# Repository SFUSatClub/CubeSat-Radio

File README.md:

# CubeSat-Radio
KiCad project of the cubesat radio test article in preparation for the Canadian Satellite Design Challenge

This repository uses the SFU Satellite Team's KiCad component library as a submodule.
To start working on the repository:

```
1. Open the git shell
2. Navigate to the directory you wish to place the repository inside
3. git clone --recursive "https://github.com/SFUSatClub/CubeSat-Radio.git"
4. cd .\CubeSat-Radio\KiCad-Lib\
5. git checkout master
```

If you modify either the component schematic or footprint libraries you must push those changes to the SFUSatClub/KiCad-Lib repository.

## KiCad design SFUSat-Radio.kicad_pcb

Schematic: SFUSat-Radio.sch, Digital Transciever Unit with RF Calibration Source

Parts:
C41, C42: 100nF; C_0402; Ratings AEC-Q200; Tolerance ±20%; Manufacturer Part Numbe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 CGA2B1X7R1C104M050BC
C413, C422, C513, C522: 39pF; C_0402; Tolerance ±5%; Voltage - Rated 50V; Manufacturer Part Numbe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 GRM1555C1H390JA01D
C414: 22pF; C_0402; Part Number GRM1555C1H220JZ01E; Digi-Key 490-11382-1-ND
C415, C416, C429, C430, C431, C432, C433, C434, C519, C529, C530, C531, C532, C533, C534: DNF; C_0402
C417, C420: 10pF; C_0402; Part Number GJM1555C1H100JB01D; Digi-Key 490-3113-1-ND
C418: 2.2uF; C_0402; Part Number JMK105BJ225MVHF; Digi-Key 587-3710-1-ND
C419, C518: 27pF; C_0402; Tolerance ±5%; Voltage - Rated 50V; Manufacturer Part Numbe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 GRM1555C1H270JA01D
C421: 1.2pF; C_0402; Part Number GJM1555C1H1R2BB01D; Digi-Key 490-8085-1-ND
C514: 7.5pF; C_0402; Tolerance ±0.1pF; Voltage - Rated 50V; Manufacturer Part Numbe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 GRM1555C1H7R5BA01D
C515: 15pF; C_0402; Tolerance ±5%; Voltage - Rated 50V; Manufacturer Part Numbe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 GJM1555C1H150JB01D
C516: 12pF; C_0402; Tolerance ±5%; Voltage - Rated 50V; Manufacturer Part Numbe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 GJM1555C1H120JB01D
C517: 10pF; C_0402; Tolerance ±5%; Voltage - Rated 50V; Manufacturer Part Numbe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 GJM1555C1H100JB01D
C520: 5.6pF; C_0402; Tolerance ±0.25pF; Voltage - Rated 50V; Manufacturer Part Numbe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 GJM1555C1H5R6CB01D
C521: 0.5pF; C_0402; Tolerance ±0.25pF; Voltage - Rated 50V; Manufacturer Part Numbe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 GJM1555C1HR50CB01D
D1, D3, D11: GREEN; LED_0603
J1: PC104-8BIT; PC104-8bit
J2, J3, J4, J5: PC104PTH
J6: SMA; SMA-Vert-TH
J7, J8, J9, J10, J11: TP_TH_150
J12, J13, J14, J400, J500: SMA; UFL-R-SMT-1-Coaxial-Connector; Digikey H9161-ND
J15, J25: Conn_01x02; Socket_Strip_Straight_1x02_Pitch2.54mm
L400: 8.2nH; L_0402; Part Number 0402CS-8N2XJLW; Digi-Key N/A
L401, L402, L403, L405: 0R0; L_0603; Part Number RMC1/16JPTP; Digi-Key N/A
L404: 12.55nH; L_1606; Part Number 1606-10J; Digi-Key N/A
L500: 2.7nH; L_0402; Manufacturer Part Numbe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 0402CS-2N7XJLW
L501, L502: 220R; L_0603; Current Rating (Max) 2A; Manufacturer Part Numbe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 BLM18EG221SN1D
L503: DNF; L_0603
L504: 5.6nH; L_1606; Manufacturer Part Numbe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 1606-6JLC
L505: 1.5nH; L_0603; Current Rating 500mA; Tolerance ±0.3nH; Manufacturer Part Numbe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 LQG18HN1N5S00D
P1: 3pin-DC-power; PJ-028-SMT-TR-3pin-DC-jack
R1, R2: 1k0-DNF; R_0402; Tolerance ±0.5%; Manufacturer Part Numbe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 ERA-2AED102X
R3, R13, R18: 287; R_0402
R600, R603, R605, R611, R612, R615: 0R; R_0402; Tolerance Jumper; Manufacturer Part Numbe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 AC0402JR-070RL
R601, R602, R604, R610, R613, R614: DNF; R_0402
U1, U400, U500: SINGLE_0402
U2: SKY13345-368LF; 12-UFQFN-PAD; Voltage - Supply 2.5 V ~ 5.5 V; Manufacturer Part Numbe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 SKY13345-368LF
U3: CD4555BPWR; TSSOP-16; Voltage - Supply 3 V ~ 18 V; Voltage Supply Source Dual Supply; Manufacturer Part Numbe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 CD4555BPWR
U101: 0433BM15A0001; U_0805-6; Mouser 609-0433BM15A0001E
U111: 0915BM15A0001E; U_0805-6; Mouser 609-0915BM15A0001E

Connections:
/3.3V Regulator/3V3OUT: J25.2; also elsewhere on the board
/3V1: J9.1, R18.1; also elsewhere on the board
/3V3: C41.1, C42.1, J1.3B, J1.29B, J8.1, J25.1, R1.1, R2.1, R3.1, R600.1, R602.1, R604.1, R610.1, R612.1, R614.1, U2.7, U3.16; also elsewhere on the board
/3V6: J7.1, L401.1, L402.1, L403.1, L501.1, L502.1, L503.1, R13.1; also elsewhere on the board
/5V0: J10.1; also elsewhere on the board
/CC1101_LB/RF_N: U101.3; also elsewhere on the board
/CC1101_LB/RF_P: U101.4; also elsewhere on the board
/CC1101_UB/RF_N: U111.3; also elsewhere on the board
/CC1101_UB/RF_P: U111.4; also elsewhere on the board
/EN_3V6: J1.12B, J15.1; also elsewhere on the board
/LB_HP_RX: U2.1; also elsewhere on the board
/LB_HP_TX: C422.1, U2.9
/LB_LP: J12.1 (INNER), U101.1; also elsewhere on the board
/LB_LP_TX: C413.2; also elsewhere on the board
/LB_RX0TX1: U3.2; also elsewhere on the board
/LB_TEST_TX: C419.1, C420.1, C421.1, C422.2, C432.1, C433.1, C434.1, L405.1
/MISO: J1.3A; also elsewhere on the board
/MOSI: J1.2A; also elsewhere on the board
/PA_LB/IN: C414.1; also elsewhere on the board
/PA_LB/OUT: C415.1, C416.1, C417.1, C429.1, C430.1, C431.1, L404.2, L405.2; also elsewhere on the board
/PA_UB/IN: C514.1; also elsewhere on the board
/PA_UB/OUT: C515.1, C516.1, C517.1, C529.1, C530.1, C531.1, L504.2, L505.1; also elsewhere on the board
/PKT_RCV: J1.5A; also elsewhere on the board
/SCL: J1.18B, R2.2; also elsewhere on the board
/SCLK: J1.1A; also elsewhere on the board
/SDA: J1.17B, R1.2; also elsewhere on the board
/Temp_sense_LB/A0: R600.2, R601.1; also elsewhere on the board
/Temp_sense_LB/A1: R602.2, R603.1; also elsewhere on the board
/Temp_sense_LB/A2: R604.2, R605.1; also elsewhere on the board
/Temp_sense_UB/A0: R610.2, R611.1; also elsewhere on the board
/Temp_sense_UB/A1: R612.2, R613.1; also elsewhere on the board
/Temp_sense_UB/A2: R614.2, R615.1; also elsewhere on the board
/UB_HP_TX: C522.1, U2.3
/UB_LP: C513.2, J13.1 (INNER), U111.1
/UB_RX0TX1: U3.3; also elsewhere on the board
/UB_TEST_TX: C519.1, C520.1, C521.1, C522.2, C532.1, C533.1, C534.1, L505.2
/V1: U2.4, U3.4
/V2: U2.5, U3.5
/V3: U2.6, U3.6
/VIN: J1.28A, J1.29A, J15.2, P1.1; also elsewhere on the board
/~LB_CS: J1.4A; also elsewhere on the board
/~UB_CS: J1.6A; also elsewhere on the board
GND: C41.2, C42.2, C415.2, C416.2, C417.2, C418.1, C419.2, C420.2, C421.2, C429.2, C430.2, C431.2, C432.2, C433.2, C434.2, C515.2, C516.2, C517.2, C518.1, C519.2, C520.2, C521.2, C529.2, C530.2, C531.2, C532.2, C533.2, C534.2, D1.1, D3.1, D11.1, J1.1B, J1.2B, J1.31B, J1.32A, J1.32B, J2.1, J3.1, J4.1, J5.1, J6.2 (OUTER), J11.1, J12.2 (OUTER), J13.2 (OUTER), J14.2 (OUTER), J400.2 (OUTER), J500.2 (OUTER), L400.2, L500.2, P1.2, P1.3, R601.2, R603.2, R605.2, R611.2, R613.2, R615.2, U2.2, U2.8, U2.10, U2.12, U2.13, U3.1, U3.8, U3.15, U101.2, U101.5, U101.6, U111.2, U111.5, U111.6; also elsewhere on the board
unnamed: C413.1, C414.2, L400.1
unnamed: C418.2, L401.2, L402.2, L403.2, L404.1
unnamed: C513.1, C514.2, L500.1
unnamed: C518.2, L501.2, L502.2, L503.2, L504.1
unnamed: D1.2, R18.2
unnamed: D3.2, R3.2
unnamed: D11.2, R13.2
unnamed: J6.1 (INNER), U2.11
unnamed: J14.1 (INNER), U1.1
unnamed: J400.1 (INNER), U400.1
unnamed: J500.1 (INNER), U500.1

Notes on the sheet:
strange pkg
to antenna
LED List: 3V3 On 3V6 On 5V0 On 3V1 On UB Transmitting LB Transmitting Packet Ready
CTRL
TX/RX Truth Table
Path
REF 10*
REF 11*
REF 4**
REF 5**
435Mhz Lower Band (LB)
790MHz Upper Band (UB)
REF 60*
REF 61*
ADDR: 0x4A
ADDR: 0x49
UB_RX0TX1
LB_RX0TX1
Antenna feed select truth table

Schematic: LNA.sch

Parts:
C3, C11: 100pF; C_0402; Part Number GRM1555C1H101JA01D; Digi-Key 490-5922-1-ND
C4, C9: 390pF; C_0402; Part Number GRM1555C1H391JA01J; Digi-Key 490-6236-1-ND
C5, C6: 0.01uF; C_0402; Part Number GRM155R71E103KA01D; Digi-Key 490-1312-1-ND
C7, C8: 56pF; C_0402; Part Number GRM1555C1H560JA01D; Digi-Key 490-1288-1-ND
C10: 0.1uF; C_0402; Part Number GRM155R71C104KA88D; Digi-Key 490-3261-1-ND
J16: SMA; UFL-R-SMT-1-Coaxial-Connector; Digikey H9161-ND
L1: 22nH; L_0402; Part Number 0402CS-22NXGLW; Digi-Key N/A
L2: 4.3nH; L_0402; Part Number 0402CS-4N3XGLW; Digi-Key N/A
L3: 24nH; L_0402; Part Number 0402CS-24NXGLW; Digi-Key N/A
R5: 0R05; C_0603; Part Number BLM18EG221SN1D; Digi-Key 490-3992-1-ND
R6: 1210; R_0402; Part Number RC0402FR-071K21L; Digi-Key 311-1.21KLRCT-ND
R7: 100; R_0402; Part Number RC0402FR-07100RL; Digi-Key 311-100LRCT-ND
U5: MML09211H; 8-VFDFN; Part Number MML09211HT1; Digi-Key MML09211HT1CT-ND
U6: SINGLE_0402

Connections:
/5V0: R5.1; also elsewhere on the board
/LB_HP_RX: C11.1; also elsewhere on the board
/LB_LP_RX: C3.2; also elsewhere on the board
GND: C4.2, C5.2, C6.2, C7.2, C9.2, C10.2, J16.2 (OUTER), U5.9; also elsewhere on the board
unnamed: C3.1, L1.1, L2.2
unnamed: C4.1, C6.1, L1.2, U5.3
unnamed: C8.1, R7.2
unnamed: C8.2, U5.5
unnamed: C5.1, C7.1, C9.1, C10.1, L3.1, R5.2, R6.1
unnamed: C11.2, L3.2, R7.1, U5.6, U5.7
unnamed: J16.1 (INNER), U6.1
unnamed: L2.1, U5.1
unnamed: R6.2, U5.4

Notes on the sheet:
Ferrite bead, 220 Ohm @ 100MHz

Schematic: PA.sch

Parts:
C401, C412: 10uF; C_TANT_1411; Tolerance ±10%; Voltage - Rated 16V; Manufacturer Part Numbe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 TAJB106K016RNJ
C402, C407, C408, C409: 1uF; C_0402; Part Number GRM155R61A105KE15D; Digi-Key 490-12701-1-ND
C403: 10uF; C_TANT_2312; Tolerance ±20%; Voltage - Rated 25V; Manufacturer Part Numbe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 TAJC106M025RNJ
C404, C410: 2.2uF; C_0402; Part Number JMK105BJ225MVHF; Digi-Key 587-3710-1-ND
C405: 0.33uF; C_0402; Tolerance ±10%; Voltage - Rated 10V; Manufacturer Part Numbe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 CL05A334KP5NNNC
C406: 220pF; C_0402; Part Number GRM1555C1H221JA01E; Digi-Key 490-1293-1-ND
C411: DNF; C_0402; Part Number GRM155R61A105KE15D; Digi-Key 490-12701-1-ND
C428, C523, C524, C525, C526, C527: DNF; C_0402
J401, J402, J404, J405, J406: TP_TH_150
R401, R409: 220R; R_0402; Part Number RMC1/16S-221JTH; Digi-Key N/A
R402, R403: 390R; R_0402; Part Number RMC1/16S-391JTH; Digi-Key N/A
R404: 1K; R_0402; Part Number RC0402JR-071KL; Digi-Key 311-1.0KJRCT-ND
R405, R406, R407, R408: 10K; R_0402; Part Number RC0402JR-0710KL; Digi-Key 311-10KJRCT-ND
R410: 100k; R_0805; Tolerance ±1%; Manufacturer Part Numbe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 ERJ-6ENF1003V
R411: DNF; R_0805
RV401: CT6EP103; Tolerance ±10%; Manufacturer Part Numbe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 CT6EP103
SH500: BMI-S-205-F; Manufacturer Part Numbe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 BMI-S-205-F
U401: LMV358; TSSOP-8_4.4x3mm_Pitch0.65mm; Part Number LMV358IYDT; Digi-Key 497-10524-1-ND
U402: RF6886; QFN-24; Part Number RF6886TR13; Digi-Key 689-1091-1-ND

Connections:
/3V1: R410.1, RV401.1, U401.8; also elsewhere on the board
/3V6: C403.1, C406.1, C409.1, C428.1, C523.1, C524.1, C525.1, C526.1, C527.1, R402.2, R403.2, U402.1, U402.2, U402.3, U402.22; also elsewhere on the board
/PA_LB/GAIN: J406.1, R410.2, R411.1, RV401.2, U401.3
/PA_LB/IN: U402.6; also elsewhere on the board
/PA_LB/OUT: U402.13, U402.14, U402.15, U402.16, U402.17, U402.18; also elsewhere on the board
/PA_LB/PWR_REF: C408.1, J405.1, R403.1, R408.1, U402.24
/PA_LB/PWR_SENSE: C407.1, J404.1, R402.1, R407.1, U402.23
/PA_LB/VREG: C401.1, C402.1, C405.2, C411.1, C412.1, J401.1, R401.2, R409.1, U401.1
GND: C401.2, C402.2, C403.2, C404.2, C406.2, C407.2, C408.2, C409.2, C410.2, C411.2, C412.2, C428.2, C523.2, C524.2, C525.2, C526.2, C527.2, R406.2, R411.2, RV401.3, SH500.1, SH500.2, SH500.3, SH500.4, SH500.5, SH500.6, SH500.7, SH500.8, SH500.9, SH500.10, SH500.11, SH500.12, SH500.13, SH500.14, SH500.15, SH500.16, SH500.17, SH500.18, SH500.19, SH500.20, U401.4, U402.7, U402.8, U402.9, U402.10, U402.11, U402.12, U402.CP; also elsewhere on the board
unnamed: C404.1, R401.1, U402.5
unnamed: C405.1, R404.2, U401.2
unnamed: C410.1, R409.2, U402.19
unnamed: J402.1, R404.1, R405.2, U401.7
unnamed: R405.1, R407.2, U401.6
unnamed: R406.1, R408.2, U401.5

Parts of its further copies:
C501, C512: 10uF; C_TANT_1411; Tolerance ±10%; Voltage - Rated 16V; Manufacturer Part Numbe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 TAJB106K016RNJ
C502, C507, C508, C509: 1uF; C_0402; Part Number GRM155R61A105KE15D; Digi-Key 490-12701-1-ND
C503: 10uF; C_TANT_2312; Tolerance ±20%; Voltage - Rated 25V; Manufacturer Part Numbe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 TAJC106M025RNJ
C504, C510: 2.2uF; C_0402; Part Number JMK105BJ225MVHF; Digi-Key 587-3710-1-ND
C505: 0.33uF; C_0402; Tolerance ±10%; Voltage - Rated 10V; Manufacturer Part Numbe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 CL05A334KP5NNNC
C506: 220pF; C_0402; Part Number GRM1555C1H221JA01E; Digi-Key 490-1293-1-ND
J501, J502, J504, J505, J506: TP_TH_150
R501, R509: 220R; R_0402; Part Number RMC1/16S-221JTH; Digi-Key N/A
R502, R503: 390R; R_0402; Part Number RMC1/16S-391JTH; Digi-Key N/A
R504: 1K; R_0402; Part Number RC0402JR-071KL; Digi-Key 311-1.0KJRCT-ND
R505, R506, R507, R508: 10K; R_0402; Part Number RC0402JR-0710KL; Digi-Key 311-10KJRCT-ND
R510: 100k; R_0805; Tolerance ±1%; Manufacturer Part Numbe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 ERJ-6ENF1003V
RV501: CT6EP103; Tolerance ±10%; Manufacturer Part Numbe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 CT6EP103
SH400: BMI-S-205-F; Manufacturer Part Numbe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 BMI-S-205-F
U501: LMV358; TSSOP-8_4.4x3mm_Pitch0.65mm; Part Number LMV358IYDT; Digi-Key 497-10524-1-ND
U502: RF6886; QFN-24; Part Number RF6886TR13; Digi-Key 689-1091-1-ND

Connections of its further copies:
/3V1: R510.1, RV501.1, U501.8; also elsewhere on the board
/3V6: C503.1, C506.1, C509.1, R502.2, R503.2, U502.1, U502.2, U502.3, U502.22; also elsewhere on the board
/PA_UB/GAIN: J506.1, R510.2, RV501.2, U501.3; also elsewhere on the board
/PA_UB/IN: U502.6; also elsewhere on the board
/PA_UB/OUT: U502.13, U502.14, U502.15, U502.16, U502.17, U502.18; also elsewhere on the board
/PA_UB/PWR_REF: C508.1, J505.1, R503.1, R508.1, U502.24
/PA_UB/PWR_SENSE: C507.1, J504.1, R502.1, R507.1, U502.23
/PA_UB/VREG: C501.1, C502.1, C505.2, C512.1, J501.1, R501.2, R509.1, U501.1; also elsewhere on the board
GND: C501.2, C502.2, C503.2, C504.2, C506.2, C507.2, C508.2, C509.2, C510.2, C512.2, R506.2, RV501.3, SH400.1, SH400.2, SH400.3, SH400.4, SH400.5, SH400.6, SH400.7, SH400.8, SH400.9, SH400.10, SH400.11, SH400.12, SH400.13, SH400.14, SH400.15, SH400.16, SH400.17, SH400.18, SH400.19, SH400.20, U501.4, U502.7, U502.8, U502.9, U502.10, U502.11, U502.12, U502.CP; also elsewhere on the board
unnamed: C504.1, R501.1, U502.5
unnamed: C505.1, R504.2, U501.2
unnamed: C510.1, R509.2, U502.19
unnamed: J502.1, R504.1, R505.2, U501.7
unnamed: R505.1, R507.2, U501.6
unnamed: R506.1, R508.2, U501.5

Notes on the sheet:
Amplifier
Output Power Feedback
Output Power Control
R*05,R*06/R*07,R*08 * (Vref - Vsense) = Vout

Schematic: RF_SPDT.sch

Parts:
C12, C14, C15: 47pF; C_0402
C13: 47nF; C_0402
J17, J18: SMA; UFL-R-SMT-1-Coaxial-Connector; Digikey H9161-ND
U7: SKY13372-467LF; QFN-16_650P
U8, U11: SINGLE_0402
U17: 74LVC1G14SE-7; SOT353; Voltage - Supply 1.65 V ~ 5.5 V; Manufacturer Part Numbe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 74LVC1G14SE-7

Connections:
/3V3: C13.1, U7.1 (VDD), U17.5; also elsewhere on the board
/LB_LP: C12.1; also elsewhere on the board
/LB_LP_RX: C15.1; also elsewhere on the board
/LB_LP_TX: C14.1; also elsewhere on the board
/LB_RX0TX1: U17.2; also elsewhere on the board
GND: C13.2, J17.2 (OUTER), J18.2 (OUTER), U7.4 (GND), U7.5 (GND), U7.6 (GND), U7.7 (GND), U7.8 (GND), U7.10 (GND), U7.11 (GND), U7.13 (GND), U7.14 (GND), U7.15 (GND), U7.16 (GND), U7.17 (PAD), U17.3; also elsewhere on the board
unnamed: C12.2, U7.3 (RFC)
unnamed: C14.2, U7.12 (J1)
unnamed: C15.2, U7.9 (J2)
unnamed: J17.1 (INNER), U11.1
unnamed: J18.1 (INNER), U8.1
unnamed: U7.2 (VCTL), U17.4

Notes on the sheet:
CTRL
TX/RX Truth Table
Path
For U6, U8, and U10, place these pads on the PCB such that they are in between the pads of C19, C20 and C21 so a jumper can be placed at a 45 degree angle to test the RF path

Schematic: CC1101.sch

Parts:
C100, C103, C105, C106, C107: 100nF; C_0402
C101: 12pF; C_0402
C102: 15pF; C_0402
C104: 220pF; C_0402
R100: 56k; R_0402
U13: CONN_02X05_SHRD; Socket_Strip_Straight_2x05; Current Rating 3A; Manufacturer Part Numbe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 SBH11-PBPC-D05-ST-BK
U100: CC1101-Q1
X100: NX3225GA

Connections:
/3V3: C100.2, C103.2, C104.2, C105.2, C107.2, U13.2, U100.6, U100.9, U100.11, U100.15, U100.18, U100.21, U100.30, U100.31; also elsewhere on the board
/CC1101_LB/RF_N: U100.13; also elsewhere on the board
/CC1101_LB/RF_P: U100.12; also elsewhere on the board
/CC1101_UB/GDO0: U13.4; also elsewhere on the board
/CC1101_UB/OP_3.3: U13.9
/CC1101_UB/~RESET: U13.7
/LB_RX0TX1: U100.28; also elsewhere on the board
/MISO: U13.10, U100.26; also elsewhere on the board
/MOSI: U13.8, U100.23; also elsewhere on the board
/PKT_RCV: U100.3; also elsewhere on the board
/SCLK: U13.6, U100.25; also elsewhere on the board
/UB_RX0TX1: U13.3; also elsewhere on the board
/~LB_CS: U100.4; also elsewhere on the board
/~UB_CS: U13.5; also elsewhere on the board
GND: C100.1, C101.1, C102.1, C103.1, C104.1, C105.1, C106.2, C107.1, R100.2, U13.1, U100.1, U100.8, U100.10, U100.14, U100.19, U100.22, U100.29, U100.33; also elsewhere on the board
unnamed: C101.2, U100.5, X100.1
unnamed: C102.2, U100.7, X100.3
unnamed: C106.1, U100.2, U100.32
unnamed: R100.1, U100.20

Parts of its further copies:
C110, C113, C115, C116, C117: 100nF; C_0402
C111: 12pF; C_0402
C112: 15pF; C_0402
C114: 220pF; C_0402
R110: 56k; R_0402
U12: CONN_02X05_SHRD; Socket_Strip_Straight_2x05; Current Rating 3A; Manufacturer Part Numbe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 SBH11-PBPC-D05-ST-BK
U110: CC1101-Q1
X110: NX3225GA

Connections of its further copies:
/3V3: C110.2, C113.2, C114.2, C115.2, C117.2, U12.2, U110.6, U110.9, U110.11, U110.15, U110.18, U110.21, U110.30, U110.31; also elsewhere on the board
/CC1101_LB/OP_3.3: U12.9
/CC1101_LB/~RESET: U12.7
/CC1101_UB/GDO0: U110.3; also elsewhere on the board
/CC1101_UB/RF_N: U110.13; also elsewhere on the board
/CC1101_UB/RF_P: U110.12; also elsewhere on the board
/LB_RX0TX1: U12.3; also elsewhere on the board
/MISO: U12.10, U110.26; also elsewhere on the board
/MOSI: U12.8, U110.23; also elsewhere on the board
/PKT_RCV: U12.4; also elsewhere on the board
/SCLK: U12.6, U110.25; also elsewhere on the board
/UB_RX0TX1: U110.28; also elsewhere on the board
/~LB_CS: U12.5; also elsewhere on the board
/~UB_CS: U110.4; also elsewhere on the board
GND: C110.1, C111.1, C112.1, C113.1, C114.1, C115.1, C116.2, C117.1, R110.2, U12.1, U110.1, U110.8, U110.10, U110.14, U110.19, U110.22, U110.29, U110.33; also elsewhere on the board
unnamed: C111.2, U110.5, X110.1
unnamed: C112.2, U110.7, X110.3
unnamed: C116.1, U110.2, U110.32
unnamed: R110.1, U110.20

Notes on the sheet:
Place decoupling capacitors as close as possible to power pins
Required Power for Debugger operation
Optional 3V3 source
Unconnected
MISO, MOSI, and SCLK signal are the same for both upper and lower band CC1101. Care must be taken to prevent interference when multiple masters are connected.

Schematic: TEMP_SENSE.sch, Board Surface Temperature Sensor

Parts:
C600: DNF; C_0402
U600: STLM75; TSSOP-8-3x3mm-SOT505-1

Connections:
/3V3: C600.1, U600.8; also elsewhere on the board
/SCL: U600.2; also elsewhere on the board
/SDA: U600.1; also elsewhere on the board
/Temp_sense_LB/A0: U600.7; also elsewhere on the board
/Temp_sense_LB/A1: U600.6; also elsewhere on the board
/Temp_sense_LB/A2: U600.5; also elsewhere on the board
GND: C600.2, U600.4; also elsewhere on the board

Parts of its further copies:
U610: STLM75; TSSOP-8-3x3mm-SOT505-1

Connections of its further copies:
/3V3: U610.8; also elsewhere on the board
/SCL: U610.2; also elsewhere on the board
/SDA: U610.1; also elsewhere on the board
/Temp_sense_UB/A0: U610.7; also elsewhere on the board
/Temp_sense_UB/A1: U610.6; also elsewhere on the board
/Temp_sense_UB/A2: U610.5; also elsewhere on the board
GND: U610.4; also elsewhere on the board

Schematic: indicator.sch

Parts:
D420, D421: GREEN; LED_0603
J23, J24: TP_TH_150
R420, R421: 287; R_0402
U420: 2N7002DW; SOT-363

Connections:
/3V3: R420.1, R421.1; also elsewhere on the board
/5V0: J24.1; also elsewhere on the board
/LB_RX0TX1: U420.5 (G1); also elsewhere on the board
/PKT_RCV: U420.2 (G2); also elsewhere on the board
/UB_RX0TX1: J23.1; also elsewhere on the board
GND: U420.1 (S2), U420.4 (S1); also elsewhere on the board
unnamed: D420.1, U420.3 (D1)
unnamed: D420.2, R420.2
unnamed: D421.1, U420.6 (D2)
unnamed: D421.2, R421.2

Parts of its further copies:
D2, D4: GREEN; LED_0603
J21, J22: TP_TH_150
R8, R14: 287; R_0402
U14: 2N7002DW; SOT-363

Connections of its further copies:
/3V3: R8.1, R14.1; also elsewhere on the board
/5V0: U14.2 (G2); also elsewhere on the board
/LB_RX0TX1: J21.1; also elsewhere on the board
/PKT_RCV: J22.1; also elsewhere on the board
/UB_RX0TX1: U14.5 (G1); also elsewhere on the board
GND: U14.1 (S2), U14.4 (S1); also elsewhere on the board
unnamed: D2.1, U14.3 (D1)
unnamed: D2.2, R8.2
unnamed: D4.1, U14.6 (D2)
unnamed: D4.2, R14.2

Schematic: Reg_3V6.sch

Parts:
C1, C2, C16, C18, C19, C20: 10uF; C_1210; Tolerance ±10%; Voltage - Rated 16V; Manufacturer Part Numbe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 EMK325BJ106KN-T
C17, C21: 1nF; C_0402; Tolerance ±10%; Voltage - Rated 16V; Manufacturer Part Numbe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 GRM155R61C102KA01D
C22: 4.7uF; C_0805; Tolerance ±10%; Voltage - Rated 10V; Manufacturer Part Numbe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 GRM219R61A475KE34D
C23: 470nF; C_0402; Tolerance ±10%; Voltage - Rated 6.3V; Manufacturer Part Numbe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 GRM155R60J474KE19D
C24: 680pF; C_0402; Tolerance ±5%; Voltage - Rated 25V; Manufacturer Part Numbe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 GRM1555C1E681JA01D
C25: 100nF; C_0402; Tolerance ±10%; Voltage - Rated 6.3V; Manufacturer Part Numbe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 GRM155R60J104KA01D
C26, C27, C28, C29, C30: 47uF; C_1206; Tolerance ±10%; Voltage - Rated 6.3V; Manufacturer Part Numbe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 GRM31CR60J476KE19L
L4: 10uH; SLF6045; Current Rating 2.7A; Tolerance ±20%; Manufacturer Part Numbe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 SLF6045T-100M1R6-3PF
R4: 49k9; R_0805; Tolerance ±1%; Manufacturer Part Numbe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 ERJ-6ENF4992V
R9: 19K1; R_0805; Tolerance ±1%; Manufacturer Part Numbe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 ERJ-6ENF1912V
R10: 3.01R; R_0402; Tolerance ±1%; Manufacturer Part Numbe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 CRCW04023R01FKED
U4: LMS3635AQRNLRQ1; LMS3635AQRNLTQ1; Digikey 296-47482-1-ND

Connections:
/3.6V Regulator/BIAS: C25.1, R10.1, U4.22
/3.6V Regulator/BOOST: C23.1, U4.2
/3.6V Regulator/FB: C24.2, R4.2, R9.1, U4.21
/3.6V Regulator/SW: C23.2, L4.1, U4.9
/3V6: C24.1, C26.1, C27.1, C28.1, C29.1, C30.1, L4.2, R4.1, R10.2; also elsewhere on the board
/EN_3V6: U4.18; also elsewhere on the board
/VIN: C1.1, C2.1, C16.1, C17.1, C18.1, C19.1, C20.1, C21.1, U4.4, U4.14, U4.15; also elsewhere on the board
GND: C1.2, C2.2, C16.2, C17.2, C18.2, C19.2, C20.2, C21.2, C22.2, C25.2, C26.2, C27.2, C28.2, C29.2, C30.2, R9.2, U4.3, U4.5, U4.6, U4.7, U4.8, U4.10, U4.11, U4.12, U4.13, U4.16, U4.20; also elsewhere on the board
unnamed: C22.1, U4.1

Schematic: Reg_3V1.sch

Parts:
C31, C32: 1uF; C_0402; Part Number GRM155R61A105KE15D; Digi-Key 490-12701-1-ND
R11: 1K; R_0402; Part Number RC0402JR-071KL; Digi-Key 311-1.0KJRCT-ND
U9: TLV702; SOT_23_5; Part Number TLV70231DBVT; Digi-Key 296-27894-1-ND

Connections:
/3V1: C32.1, U9.5; also elsewhere on the board
/3V6: C31.1, R11.1, U9.1; also elsewhere on the board
GND: C31.2, C32.2, U9.2; also elsewhere on the board
unnamed: R11.2, U9.3

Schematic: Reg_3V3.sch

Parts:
C33: 100nF; C_0402
C34: DNF; C_0402
C35: 2.2uF; C_0402; Ratings AEC-Q200; Tolerance ±20%; Manufacturer Part Numbe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 JMK105BJ225MVHF
R12: 1k; R_0402
U10: TPS799; PDSO-G5

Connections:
/3.3V Regulator/3V3OUT: C35.1, U10.5 (OUT); also elsewhere on the board
/3V6: C33.1, R12.2, U10.1 (IN); also elsewhere on the board
GND: C33.2, C34.2, C35.2, U10.2 (GND); also elsewhere on the board
unnamed: C34.1, U10.4 (NR)
unnamed: R12.1, U10.3 (EN)

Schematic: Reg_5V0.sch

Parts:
C36: 2.2uF; C_0805; Tolerance ±10%; Voltage - Rated 10V; Manufacturer Part Numbe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 GRM21BR71A225KA01L
C37: 22uF; C_1206; Tolerance ±20%; Voltage - Rated 10V; Manufacturer Part Numbe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 GRM31CR61A226ME19L
C38: 100nF; C_0402; Ratings AEC-Q200; Tolerance ±20%; Manufacturer Part Numbe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 CGA2B1X7R1C104M050BC
C39: 10nF; C_0402; Tolerance ±10%; Voltage - Rated 10V; Manufacturer Part Numbe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 GRM155R61A103KA01D
C40: 1uF; C_0402; Part Number GRM155R61A105KE15D; Digi-Key 490-12701-1-ND
L5: 10uH; SLF7045; Current Rating 1.78A; Tolerance ±20%; Manufacturer Part Numbe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 SLF7045T-100M1R3-PF
R15: 100k; R_0805; Tolerance ±1%; Manufacturer Part Numbe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 ERJ-6ENF1003V
R16: 2.37M; R_0402; Tolerance ±1%; Manufacturer Part Numbe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 CRCW04022M37FKED
R17: 383k; R_0402; Tolerance ±1%; Manufacturer Part Numbe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 CRCW0402383KFKED
U15: TPS62175DQCR; WSON-10; Voltage - Input (Max) 28V; Voltage - Input (Min) 4.75V; Manufacturer Part Numbe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 TPS62175DQCR
U16: TPS71750DSER; WSON-6; Voltage - Input (Max) 6.5V; Voltage - Output (Min/F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 5V; Manufacturer Part Numbe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 TPS71750DSER

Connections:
/5V0: C40.1, U16.1; also elsewhere on the board
/5V Regulator/5V8: C37.1, C38.1, L5.2, R15.1, R16.1, U15.8, U15.10, U16.4, U16.6
/5V Regulator/SW_5V8: L5.1, U15.9
/VIN: C36.1, U15.2, U15.3; also elsewhere on the board
GND: C36.2, C37.2, C38.2, C39.2, C40.2, R17.2, U15.1, U15.6, U15.EP, U16.2, U16.5; also elsewhere on the board
unnamed: C39.1, U16.3
unnamed: R15.2, U15.7
unnamed: R16.2, R17.1, U15.5

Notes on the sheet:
Manual Enable?

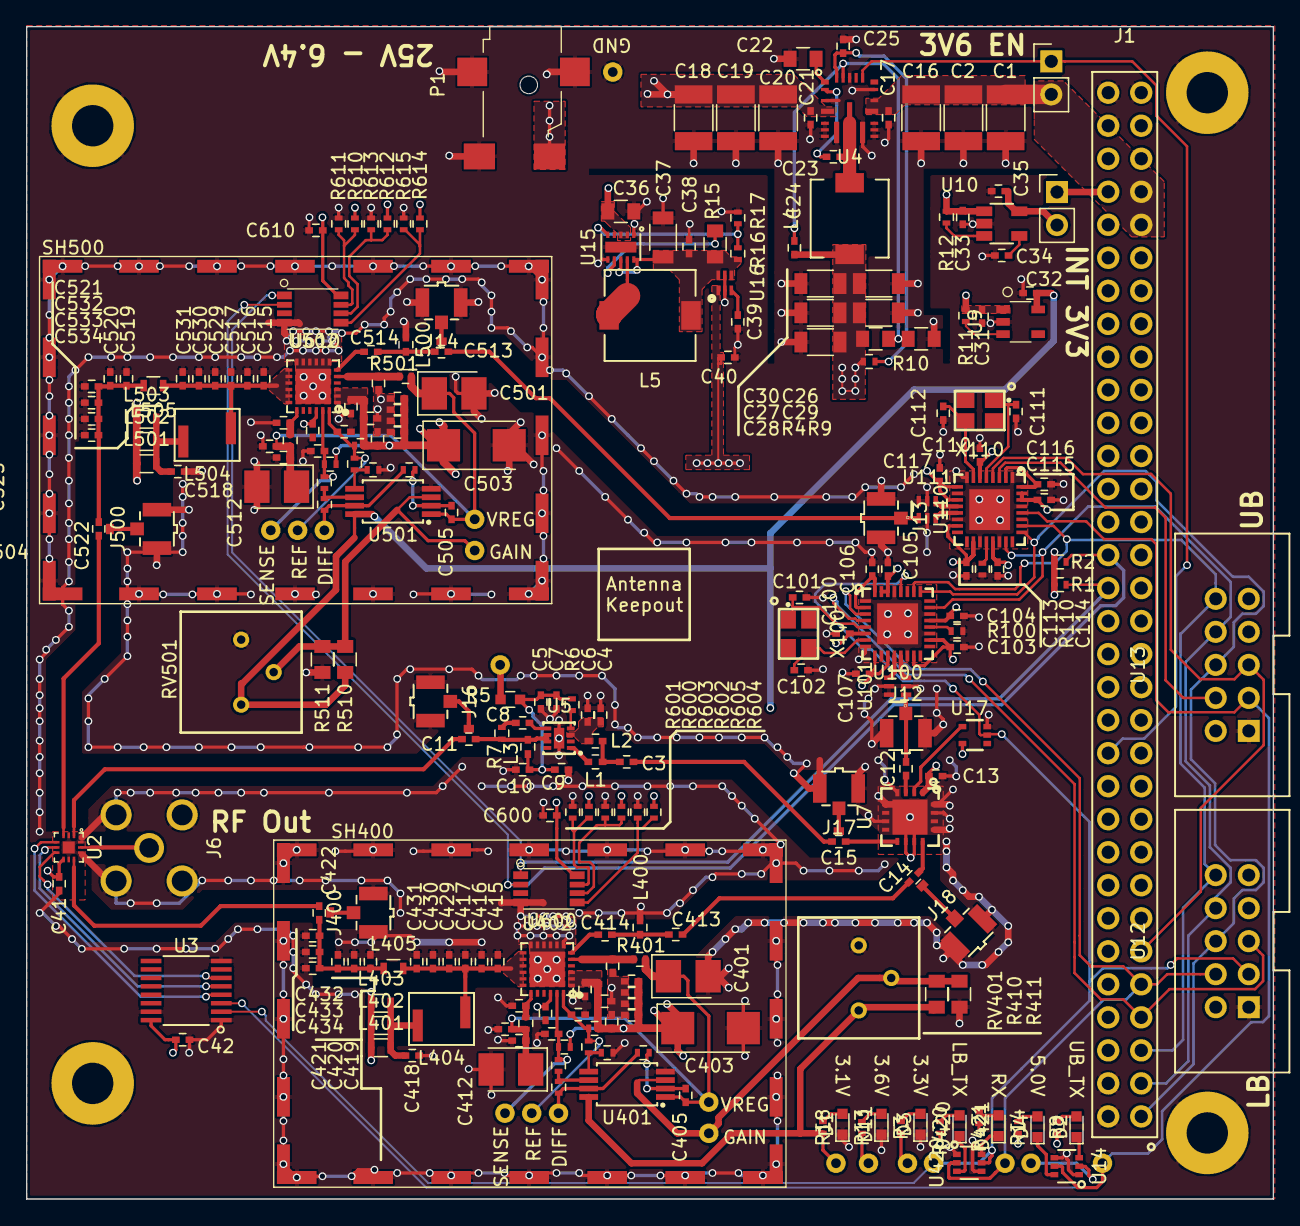
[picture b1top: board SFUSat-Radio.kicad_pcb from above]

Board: 4 copper layers, 95.9 x 90.2 mm, 280 parts (0 on the bottom side), 120 nets.

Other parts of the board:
C423, C424, C425, C426, C427, C511, C528, C610: DNP; C_0402
R511: DNP; R_0805

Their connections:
/3V3: C610.1; also elsewhere on the board
/3V6: C423.1, C424.1, C425.1, C426.1, C427.1, C528.1; also elsewhere on the board
/PA_UB/GAIN: R511.1; also elsewhere on the board
/PA_UB/VREG: C511.1; also elsewhere on the board
GND: C423.2, C424.2, C425.2, C426.2, C427.2, C511.2, C528.2, C610.2, R511.2; also elsewhere on the board

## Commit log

2017-01-03 took out the mcu schematic, fixed transciever for separate tx rx ports
2017-01-03 added power sheet for linear regulator
2017-01-04 added Vdd pins to Transciever and amplifier modules
2017-01-07 deleted MCU schematic for v0.1. Added power sub-schematic
2017-01-08 added SKY65366-21 schematic and footprint to library. Populated front end schematic with SKY and peripherial components. Added 3V6 output for power sub-schematic.
2017-01-08 added BALF-112X-02D3 to component library and to transciever sub-schematic
2017-01-08 cleanup
2017-01-09 Added RF switch to transciever schematic
    -Removed SMA lib pointing to Tobi's downloads
    -Added SKY13372-467LF to the library (symbol and decal)
    -Renamed signal “TX_SW” on RF front end page to “TRX_SIG”
    -Re-aligned some part names and reference designators
    -Added some component values to the front end
2017-01-09 Added XOSC
    -Changed the VDD pin of the RF switch to a power input
    -Added the XOSC (symbol and footprint)
    -Made some modifications to the transceiver page
2017-01-10 Fixed XOSC
    -Changed 3V3 rail of XOSC to 1V8 as specified in datasheet
    -Changed XOSC capacitor values to match the datasheet
    -Added 1V8 rail to SFUSat-Radio.sch Transceiver and Power pages
2017-01-12 added jumpers for regulater EN and a jumper for fixing PA_ADJ. Connceted TRX_SIG to GPIO0
2017-01-12 deleted TRX_OPEN net
2017-01-13 Added schematic of RT9183HGM5 (TO263-5)
2017-01-14 Added sch of TPS799 onto power sch
2017-01-15 moved jumpers into respective schematics
2017-01-15 added switches for various option and nmos array to control status leds
2017-01-15 added a bunch of footprints and generated layout file
2017-01-15 deleted a useless switch
2017-01-15 setup netclasses and added more footprints
2017-01-16 began RF chain
2017-01-16 project files till workbut names are messed up
2017-01-19 fixed filesystem
2017-01-19 added some test points
2017-01-20 layed out all components
2017-01-20 placed connectors
2017-01-22 continued routing
2017-01-23 Checked changes from botched commit
    -R5 and R6 are gone as desired
    -C4 changed from 10 nF to 100 nF looks good
    -Split up nets between pins 27 and 28 so each have their own dedicated
    capacitor
    -Added C9 to pin 28 and forward annotated it into the layout
2017-01-24 added all the gnd and pwr planes
2017-01-24 added power connector, nets connected in layout
2017-01-24 Mirrored changes from "Replaced XOSC" (fdb08e0)
    -Changed value of C5 from 10nF to 1nF
    -Added 0 ohm jumper R4 to XOSC supply rail
    -Added C13 to separate decoupling caps on pins 27 and 28
    -Added C33 to separate decoupling caps on pins 12 and 13
    -Forward annotated changes
2017-01-25 new passives added
2017-01-25 trace width changed with coplanar waveguide calculations in mind
2017-01-26 fixed rf track to match coplanar calculations, added ground vias
2017-01-26 Swapped capacitor footprints
    -Changed C27 and C37 from 0402 to 0603_HandSoldering
    -Changed C34 and C39 from 0402 to 1210_HandSoldering
2017-01-26 added back side copper to edge mounted sma footprint
2017-01-26 stencil excludes sma and rf shield pads
2017-01-28 added resized caps to layout
2017-01-30 changed via in pad to 10mil drill hole
2017-01-30 changed via to gnd net
2017-02-01 added stencil aperture to CC1125 and SKY65366
2017-02-01 modified soldermask
2017-02-01 generated gerbers
2017-02-01 fixed soldermask on CC1125
2017-02-01 added thermal pads
2017-02-02 moved via in pad to avoid stencil aperture, added pin 1 markers to a few footprints
2017-02-03 Added pull ups
    1K pull ups added on EN of DC-DC regulators and EN of front -end
2017-02-03 Added pull ups to layout
2017-02-03 Fixed component ref
2017-02-04 rev_1
2017-02-04 added paste on 1206 cap
2017-05-06 configured all libraries to use git submodules
2017-05-06 deleted old library
2017-05-07 added component documentation and BOM
2017-05-09 added doc image for CC debugger
2017-05-10 added gitignore
2017-05-11 added reset tactile switch
2017-05-12 Deleted the PCB and annotated the schematic
    Since we're going to be using a new XCVR IC, we need to re-design the PCB
2017-05-22 Added CC1101 balun, updated README.md
    Added a note to the 'README.md' file explaining how to properly clone and set up the KiCad library submodule
2017-05-22 Forgot to save before I committed the balun
2017-05-22 Updated README.md for CubeSat-Radio-v0.1
2017-05-23 added CC1101, fixed mission symbols
2017-05-27 Started added CC1101-Q1 components
2017-05-27 Added CC1101-Q1 to submodule
2017-05-27 added -rescue.lib to gitignore
2017-05-27 fixed rescue library
2017-05-28 PC104 board outline
2017-05-28 Added CC1101-Q1 and supporting components
    Also added the pad that routes to the SMA for RF path testing
2017-05-28 Removed SW1
    CC1101-Q1 has no reset pin, so no point in having a reset switch
2017-05-28 Renumbered reference designators
2017-05-31 pulled SKY en high, replaced BYP with jump
2017-05-31 Updated schematic and layout
    Added extra decoupling caps based on TI feedback and forward annotated changes to the PCB
2017-05-31 Added CC1101 datasheet
2017-05-31 Changed C25 and C26 from 0.1uF to 100nF
2017-06-01 rotated PC104 conn
2017-06-02 Updated debug connector footprint in pcbNew
2017-06-02 Removed SFU-Radio-rescue library from lib path
2017-06-02 Updated debug connector again
2017-06-02 all leds green, fixed VPC ctrl
2017-06-04 added TVS
2017-06-06 microstrip layed out
2017-06-06 route 3v3
2017-06-08 debug connector
2017-06-09 fixed 3v3 reg footprint
2017-06-09 layout complete
2017-06-09 Changed R12 and R13 to 287 ohms
2017-06-09 added IC pad via stitching
2017-06-09 added labels
2017-06-10 fixed labels, via stitching
2017-06-10 more via stitching
2017-06-10 placed component ref
2017-06-10 added TVS to TP
2017-06-10 IC->passive pad 30mil clearance
2017-06-10 added PCBway info
2017-06-11 fixed microstrip
2017-06-11 added TVS on op_3v3
2017-06-11 added pcb substrate datasheet
2017-06-12 regen gerbers
2017-06-12 gerber fixes
2017-06-12 fixed CC1101 stencil
2017-06-14 update Dk value
2017-06-14 changed RF to 0.6mm track w
2017-06-14 some ground filling
2017-06-14 ANT microstrip 0.85mm width
2017-06-14 updated fab notes
2017-06-14 generate final gerber
2017-06-14 moved gerber zip
2017-06-15 added b.mask
2017-12-25 Added 3D models for J6 and J1. See Kicad-Lib commit c9457c5d894628088f6aa1cc63c8179390a49ea0 for more detail.
2018-01-12 Updated README
    Changed everything from "CubeSat-Radio-v0.1" to "CubeSat-Radio-v0.1"
2018-01-12 Added PA, Diplexer, and LNA schematics. All three were copied over from the Amp_dev project. The PA and LNA schematics need extensive work.
2018-01-12 Updated Fab file for Rev 3. PCB will be 4 layers. The stackup is shown in Fab/PCBWay_Fab.txt copied from the official PCBWay stackup document provided via email.
2018-01-12 Added note on microstrip width. Calculated according to the stackup as provided in PCBWay_fab.txt
2018-01-19 Added new sheets
    Started adding hierarchical sheets for high and low band components
2018-02-27 included all new sfusat libraries
2018-03-02 Replaced SMA with u.fl for debug ports
2018-03-05 consolidated PA to one sch for both bands
2018-03-05 setup hierarchical sheets for transiever, SPDT switch, and PA. This configuration uses duplicate sheets to automate layout and ease schematic reading
2018-03-05 layed out upper band and lower band schematic. Need to add a 2W rated SPDT switch to connect the RX and TX stages together before the diplexer
2018-03-05 Debug SPI port for CC1101 added to CC1101.sch
2018-03-05 added 2 temp sensors for the 2 PAs
2018-03-05 setup design rules and stackup
2018-03-05 added test points
2018-03-18 Added SP3T and 2:4 decoder
2018-03-19 Added truth table for antenna feed selection
2018-03-22 Added UB PA components
2018-03-23 Fixed rescue-lib components and CONN_02X05
2018-03-24 Numbered PA reference designators
2018-03-24 Changed temp sense reference designator prefix
    Initally overlapped with PA LB reference designator prefix
2018-03-24 Annotated the schematics
2018-03-28 added 3v6 and 5v0 schematic
2018-03-30 Started PA schematic
2018-03-30 Fixed the components for the PA LB section
    Fix the PA UB section next
2018-03-31 removed rescue library
2018-03-31 power schematic complete
2018-04-01 layed out power system
2018-04-01 removed PA feedback jumper
2018-04-01 layed out CC1101 and LNA
2018-04-04 Added extra DNP filter caps for PAs
    Also confirmed PA UB components and updated Google Sheet
2018-04-06 Continued PA routing
2018-04-09 PA nearly done
2018-04-10 Added PA shield
2018-04-10 Essentially done PA
2018-04-11 Before PA clone
2018-04-11 Cloned PA layout
2018-04-11 Fixed a couple DRCs
2018-04-17 Continued RF routing
2018-04-18 Added inverter and new pots
2018-04-20 added solder mask webbing info
2018-04-20 Closes 45
2018-04-22 updated 3d model to include POT, RF Can, and inductors
2018-04-23 layed out planes around regulator. The default clearance for poly was set to 1.27 mm but PCBway requires a minimum track spacing of 0.1524mm
2018-04-23 layed out temp sensor
2018-04-23 decoupling to RF switch
2018-04-23 Improved fill around RF ICs, placed additional filter caps for UB_PA
2018-04-24 added optional gain select resistor
2018-04-24 placed optional PA filtering to LB
2018-04-24 layed out indicator lights
2018-04-24 fixed LB cc1101 test point
2018-04-24 Added barrel jack for Vin; closes 46
2018-04-24 Continued power floods
2018-04-24 More power plane routing
2018-04-24 More power plane routing (forgot to save last one)
2018-04-25 Major floods added
2018-04-25 Some more routing
2018-04-26 removed op_3v3, routed SPI
2018-04-26 routing complete
2018-04-26 changed clearance of all planes to 0.2mm. 0.1524mm is too close to PCBway's manufacturable limit
2018-04-26 modified proposed pot schematic
2018-04-26 added antenna connector keepout
2018-04-27 modified gain control circuit in following issue #54
2018-04-27 Changed microstrip width, added no fill zone around microstrip. Closes issue #52
2018-04-27 added christmas stitching
2018-04-27 placed reference designator
2018-04-27 board labeling
2018-04-27 reduced via stiching density to open up 3v6 power plane
2018-04-27 soldermask width complies with minimum 150um
2018-04-27 increased anti-pad clearance to 0.1524mm
2018-04-27 maximized balun paste aperture size
2018-04-28 changed C38 to 0402 to consolidate bom
2018-04-28 changed C35 to 0402 for bom consolidation
2018-04-28 changed C40 to 0402 for bom consolidation
2018-04-28 bom complete
2018-04-28 close issue #50
2018-04-30 gen gerbers
2018-04-30 final cleanup and check
2018-05-04 fixed BoM
2018-05-07 Changed 'DNP' to 'DNF' for new BOM tool
2018-05-15 Added fab drawing
2018-06-02 Updated components missing courtyard, assy dwgs., etc.
2018-06-11 Started proper assembly drawing
2018-06-11 Updated assembly drawing
2018-06-11 Updated courtyards
2018-06-11 Updated BOM slightly
2018-06-11 Added bom.ini for automatic BOM generator tool
2018-06-12 Added UChoice BOM
2018-06-12 Updated attributes for pick and place
2018-06-12 Closes #58
2018-06-12 Consolidated drill files
2018-06-12 Added more fabrication outputs
2018-06-12 Changed R5 value to 220R
2018-06-12 Added readme file for UChoice
